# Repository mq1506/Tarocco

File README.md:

# Tarocco-Lite
Low current version of the Tarroco board. Utilizes the DRV8801

----------------------------------------------------------------------
Based on the Tarocco (c) by Gino Magarotto

Tarocco-Lite is licensed under a
Creative Commons Attribution-ShareAlike 3.0 Unported License.

You should have received a copy of the license along with this
work.  If not, see <http://creativecommons.org/licenses/by-sa/3.0/>.

----------------------------------------------------------------------
Based upon the Tarroco board

Please buy one and support the creator on https://www.crowdsupply.com/citrus-cnc/tarocco

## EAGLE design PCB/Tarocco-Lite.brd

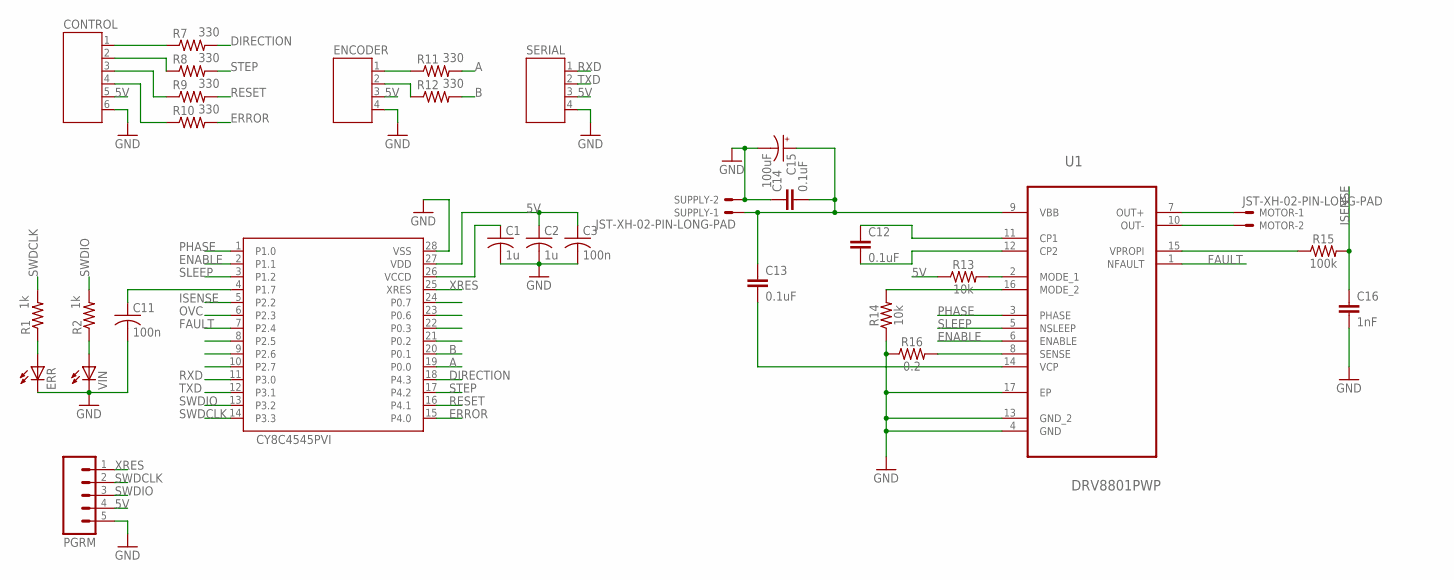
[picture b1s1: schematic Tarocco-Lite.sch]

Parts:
C1, C2: 1u; C0603
C3, C11: 100n; C0603
C12, C13, C14: 0.1uF; 0603
C15: 100uF; PANASONIC_D
C16: 1nF; 0603
CONTROL: JST-PH6
ENCODER: JST-PH4
ERR: LEDCHIP-LED0603; CHIP-LED0603
IC1: CY8C4545PVI; SSOP28
MOTOR: JST-XH-02-PIN-LONG-PAD; JST-XH-02-PACKAGE-LONG-PAD
PGRM: M05SMD2; 1X05-1MM-RA
R1, R2: 1k; R0603
R7, R8, R9, R10, R11, R12: 330; R0603
R13, R14: 10k; 0603
R15: 100k; 0603
R16: 0.2; 1210
SERIAL: JST-PH4
SUPPLY: JST-XH-02-PIN-LONG-PAD; JST-XH-02-PACKAGE-LONG-PAD
U1: DRV8801PWP; SOP65P640X120-17N
VIN: LEDCHIP-LED0603; CHIP-LED0603

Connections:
5V: C2.1, C3.1, CONTROL.5, ENCODER.3, IC1.27 (VDD), PGRM.4, R13.1, SERIAL.3
A: IC1.19 (P0.0), R11.2
B: IC1.20 (P0.1), R12.2
DIRECTION: IC1.18 (P4.3), R7.2
ENABLE: IC1.2 (P1.1), U1.6 (ENABLE)
ERROR: IC1.15 (P4.0), R10.2
FAULT: IC1.7 (P2.4), U1.1 (NFAULT)
GND: C1.2, C2.2, C3.2, C11.2, C14.1, C15.-, C16.2, CONTROL.6, ENCODER.4, ERR.C, IC1.28 (VSS), PGRM.5, R14.1, R16.1, SERIAL.4, SUPPLY.2, U1.4 (GND), U1.13 (GND_2), U1.17 (EP), VIN.C
ISENSE: C16.1, IC1.5 (P2.2), R15.2
unnamed: ENCODER.1, R11.1
unnamed: R13.2, U1.2 (MODE_1)
unnamed: ENCODER.2, R12.1
unnamed: CONTROL.1, R7.1
unnamed: CONTROL.2, R8.1
unnamed: C1.1, IC1.26 (VCCD)
unnamed: CONTROL.3, R9.1
unnamed: CONTROL.4, R10.1
unnamed: ERR.A, R1.1
unnamed: R2.1, VIN.A
unnamed: R15.1, U1.15 (VPROPI)
unnamed: C12.1, U1.11 (CP1)
unnamed: C11.1, IC1.4 (P1.7)
unnamed: C12.2, U1.12 (CP2)
unnamed: C13.2, U1.14 (VCP)
unnamed: R14.2, U1.16 (MODE_2)
OVC: IC1.6 (P2.3)
PHASE: IC1.1 (P1.0), U1.3 (PHASE)
RESET: IC1.16 (P4.1), R9.2
RXD: IC1.11 (P3.0), SERIAL.1
SENSE: R16.2, U1.8 (SENSE)
SLEEP: IC1.3 (P1.2), U1.5 (NSLEEP)
STEP: IC1.17 (P4.2), R8.2
SWDCLK: IC1.14 (P3.3), PGRM.2, R1.2
SWDIO: IC1.13 (P3.2), PGRM.3, R2.2
TXD: IC1.12 (P3.1), SERIAL.2
VBB: C13.1, C14.2, C15.+, SUPPLY.1, U1.9 (VBB)
VMOT+: MOTOR.1, U1.7 (OUT+)
VMOT-: MOTOR.2, U1.10 (OUT-)
XRES: IC1.25 (XRES), PGRM.1

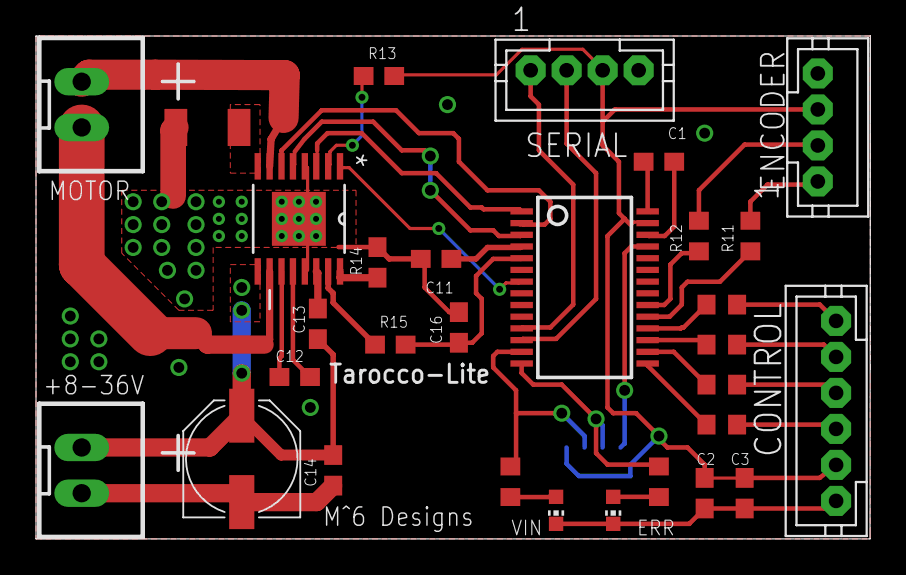
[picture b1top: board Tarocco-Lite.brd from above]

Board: 2 copper layers, 46.4 x 27.9 mm, 32 parts (1 on the bottom side), 38 nets.

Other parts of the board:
U$1: OSHW-LOGO-L_COPPER

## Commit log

2017-01-23 Initial Commit of Schematic
2017-01-23 Starting BRD from scratch
2017-01-23 Time to sleep, routing is hard
2017-01-23 Rename and mostly routed
2017-01-23 Alpha finished
2017-01-23 Added Image
2017-01-24 BOM and labelling update
2017-01-24 SO MUCH CLEANER
    Cleaned up a lot of the layout to reduce crosstalk
2017-01-24 SMD cap swap
2017-01-24 Moved bootloader location for functionality added proper BOM
2017-01-24 ground pour

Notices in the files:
parts and their libraries:
SparkFun-Capacitors: Licensing: Creative Commons ShareAlike 4.0 International - https://creativecommons.org/licenses/by-sa/4.0
